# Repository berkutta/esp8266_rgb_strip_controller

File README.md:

ESP8266 RGB Strip Controller
================

This is a simple ESP8266 based RGB Strip Controller for common color LED strips. It is designed for LED strips which have a common +12V and a negative Pin for each color. But it can also be used to switch single color LED strips or other appliances which don't exceed the current of 6A per Channel.

The Controller can be powered by a 12V DC Jack. Center positive.

### Programming

Programming is possible with `esptool` and a standard 3.3V UART Port. Connect TX and RX crossed with your UART Port, bridge the GPIO0 pad to GND and connect Power to it. Afterwards you can loose the GPIO0 to GND connection and let `esptool` upload the Firmware.

### Enclosure

In the folder `enclosure` are 3D files for a 3D printable enclosure.

### Assembly

Except the DC Jack all parts are available in the Assembly Service of JLCPCB. The DC Jack can be ordered together with the JLCPCB Order on LCSC.

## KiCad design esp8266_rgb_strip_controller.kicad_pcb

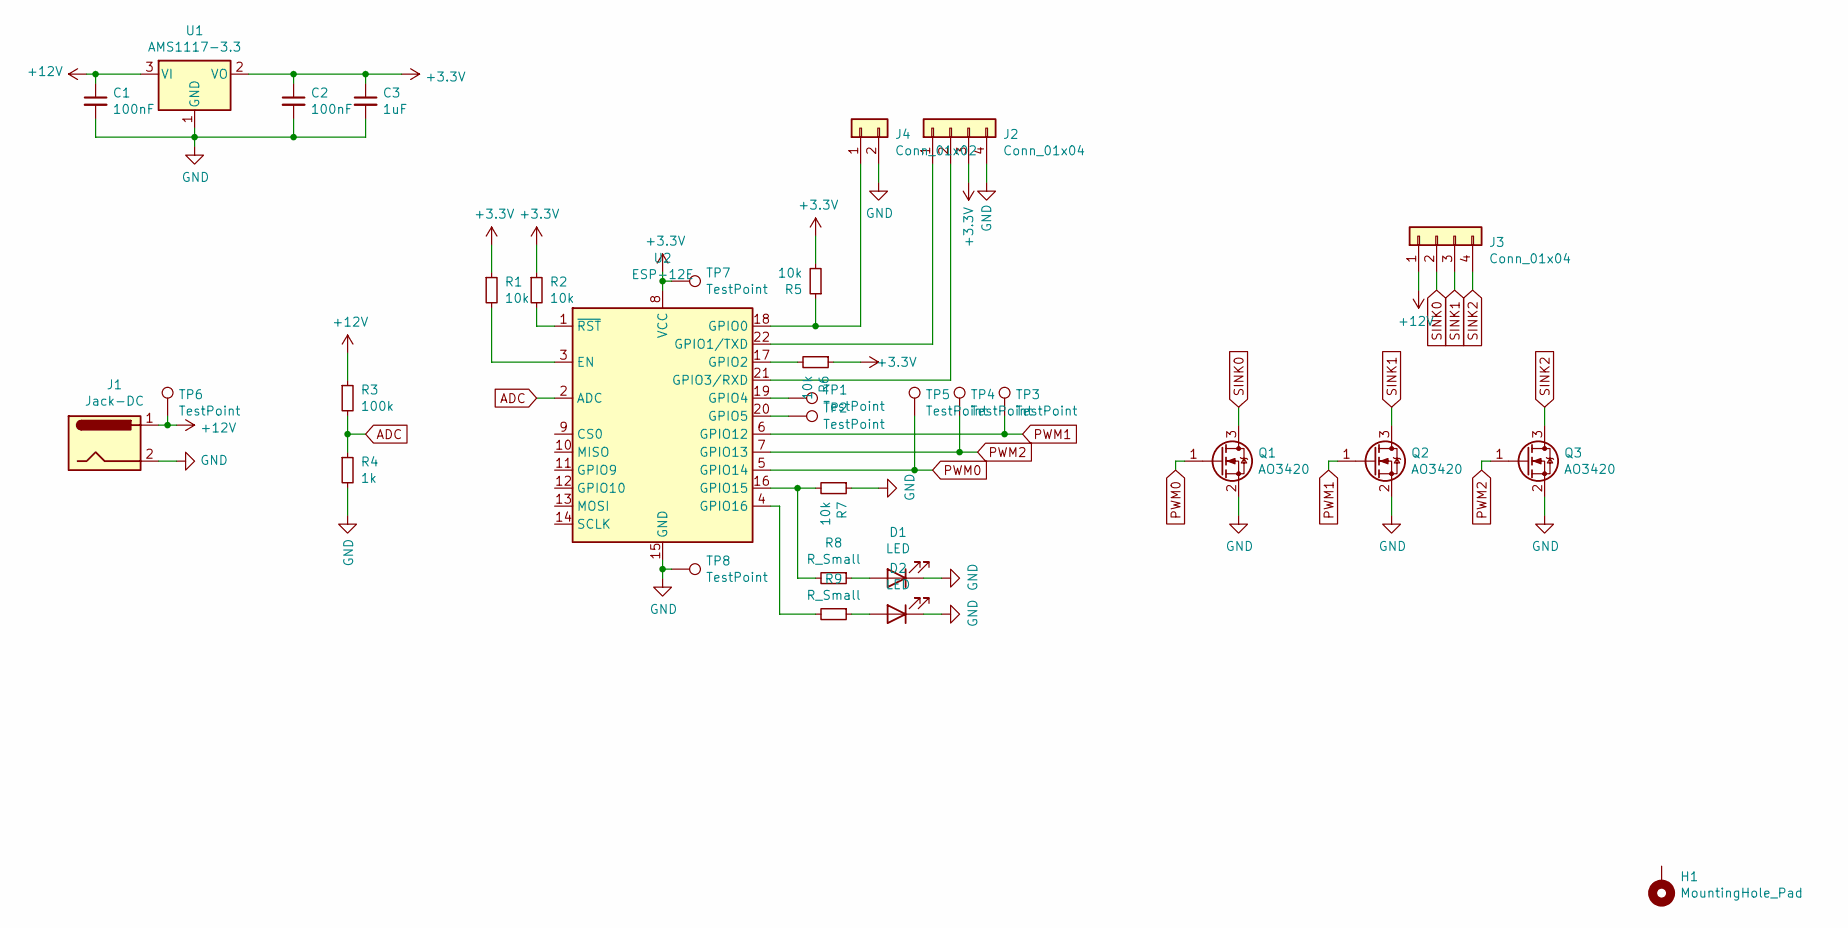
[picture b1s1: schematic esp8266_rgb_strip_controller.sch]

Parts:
C1, C2: 100nF; C_0603_1608Metric; LCSC C14663
C3: 1uF; C_0603_1608Metric; LCSC C15849
D1: LED; LED_0603_1608Metric; LCSC C72041
D2: LED; LED_0603_1608Metric; LCSC C72043
H1: MountingHole_Pad; MountingHole_2.7mm_M2.5
J1: Jack-DC; pj-051b; LCSC C388627
J2: Conn_01x04; prog_header
J3: Conn_01x04; PinHeader_1x04_P2.54mm_Vertical
J4: Conn_01x02; prog_boot_header
Q1, Q2, Q3: AO3420; SOT-23; LCSC C181095
R1, R2, R5, R6, R7: 10k; R_0603_1608Metric; LCSC C25804
R3: 100k; R_0603_1608Metric; LCSC C25803
R4: 1k; R_0603_1608Metric; LCSC C21190
R8, R9: R_Small; R_0603_1608Metric; LCSC C25804
TP1, TP2, TP3, TP4, TP5, TP6, TP7, TP8: TestPoint; TestPoint_Pad_D1.0mm
U1: AMS1117-3.3; TO-252-2; LCSC C6186
U2: ESP-12E; LCSC C82891

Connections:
+3V3: C2.1, C3.1, J2.3, R1.1, R2.1, R5.2, R6.1, TP7.1, U1.2 (VO), U2.8 (VCC)
+12V: C1.1, J1.1, J3.1, R3.1, TP6.1, U1.3 (VI)
ADC: R3.2, R4.1, U2.2 (ADC)
GND: C1.2, C2.2, C3.2, D1.1 (K), D2.1 (K), J1.2, J2.4, J4.2, Q1.2 (S), Q2.2 (S), Q3.2 (S), R4.2, R7.1, TP8.1, U1.1 (GND), U2.15 (GND)
unnamed: D1.2 (A), R8.1
unnamed: D2.2 (A), R9.1
unnamed: J2.1, U2.22 (GPIO1/TXD)
unnamed: J2.2, U2.21 (GPIO3/RXD)
unnamed: J4.1, R5.1, U2.18 (GPIO0)
unnamed: R1.2, U2.3 (EN)
unnamed: R2.2, U2.1 (~RST)
unnamed: R6.2, U2.17 (GPIO2)
unnamed: R7.2, R8.2, U2.16 (GPIO15)
unnamed: R9.2, U2.4 (GPIO16)
unnamed: TP1.1, U2.19 (GPIO4)
unnamed: TP2.1, U2.20 (GPIO5)
PWM0: Q1.1 (G), TP5.1, U2.5 (GPIO14)
PWM1: Q2.1 (G), TP3.1, U2.6 (GPIO12)
PWM2: Q3.1 (G), TP4.1, U2.7 (GPIO13)
SINK0: J3.2, Q1.3 (D)
SINK1: J3.3, Q2.3 (D)
SINK2: J3.4, Q3.3 (D)

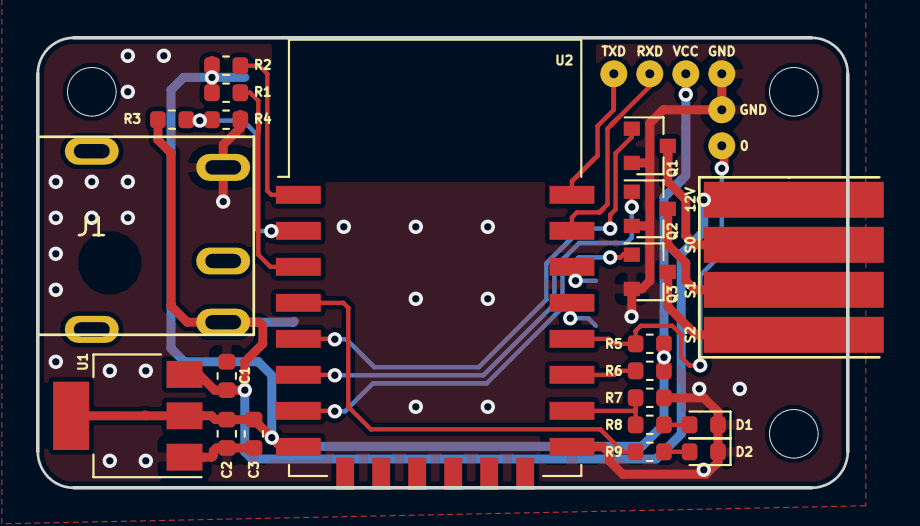
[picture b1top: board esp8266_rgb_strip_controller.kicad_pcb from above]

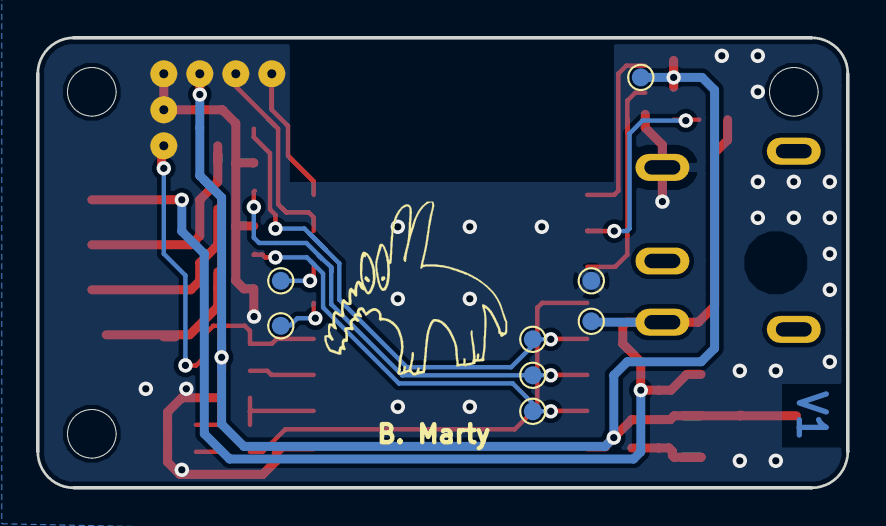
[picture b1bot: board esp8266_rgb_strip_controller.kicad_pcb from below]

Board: 2 copper layers, 45.0 x 25.0 mm, 34 parts (8 on the bottom side), 22 nets.

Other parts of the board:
H2, H3: MountingHole_Pad; MountingHole_2.7mm_M2.5

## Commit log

2021-05-19 add enclosure
2021-05-19 add docs
